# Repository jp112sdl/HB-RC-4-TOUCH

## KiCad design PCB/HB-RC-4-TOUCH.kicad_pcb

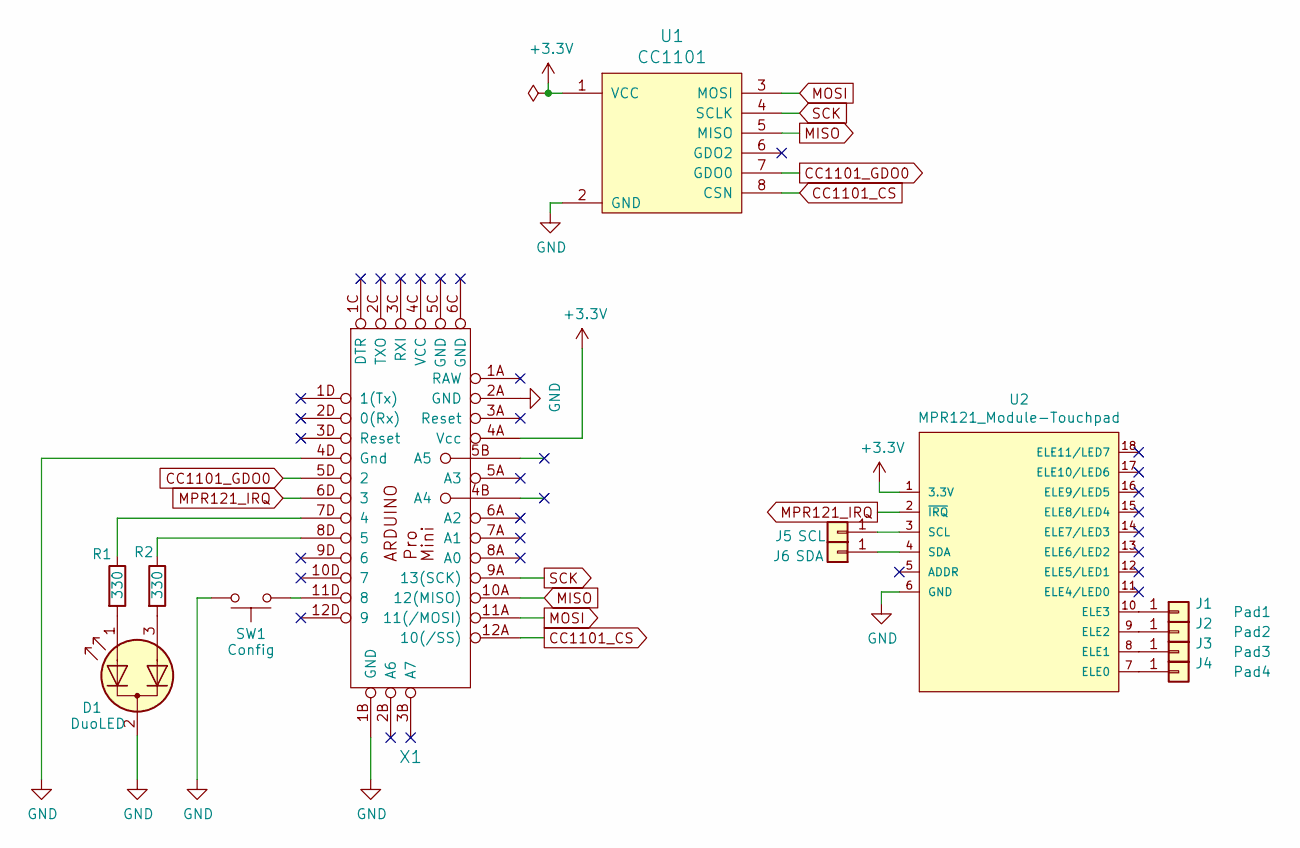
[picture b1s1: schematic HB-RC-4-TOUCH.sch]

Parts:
D1: DuoLED; LED_D3.0mm-3
J1: Pad1; TOUCH_PAD_46x46
J2: Pad2; TOUCH_PAD_46x46
J3: Pad3; TOUCH_PAD_46x46
J4: Pad4; TOUCH_PAD_46x46
J5: SCL; TestPoint_Pad_1.5x1.5mm
J6: SDA; TestPoint_Pad_1.5x1.5mm
R1, R2: 330; R_0805_2012Metric_Pad1.15x1.40mm_HandSolder
SW1: Config; SW_SPST_FSMSM
U1: CC1101; CC1101_Pads
U2: MPR121_Module-Touchpad; MPR121_SMD
X1: Arduino_Pro_Mini

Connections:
+3V3: U1.1 (VCC), U2.1 (3.3V), X1.4A (Vcc)
CC1101_CS: U1.8 (CSN), X1.12A (10(/SS))
CC1101_GDO0: U1.7 (GDO0), X1.5D (2)
GND: D1.2 (K), SW1.2, U1.2 (GND), U2.6 (GND), X1.1B (GND), X1.2A (GND), X1.4D (Gnd)
MISO: U1.5 (MISO), X1.10A (12(MISO))
MOSI: U1.3 (MOSI), X1.11A (11(/MOSI))
MPR121_IRQ: U2.2 (~IRQ), X1.6D (3)
unnamed: D1.1 (A1), R1.2
unnamed: D1.3 (A2), R2.2
unnamed: J1.1, U2.10 (ELE3)
unnamed: J2.1, U2.9 (ELE2)
unnamed: J3.1, U2.8 (ELE1)
unnamed: J4.1, U2.7 (ELE0)
unnamed: J5.1, U2.3 (SCL)
unnamed: J6.1, U2.4 (SDA)
unnamed: R1.1, X1.7D (4)
unnamed: R2.1, X1.8D (5)
unnamed: SW1.1, X1.11D (8)
SCK: U1.4 (SCLK), X1.9A (13(SCK))

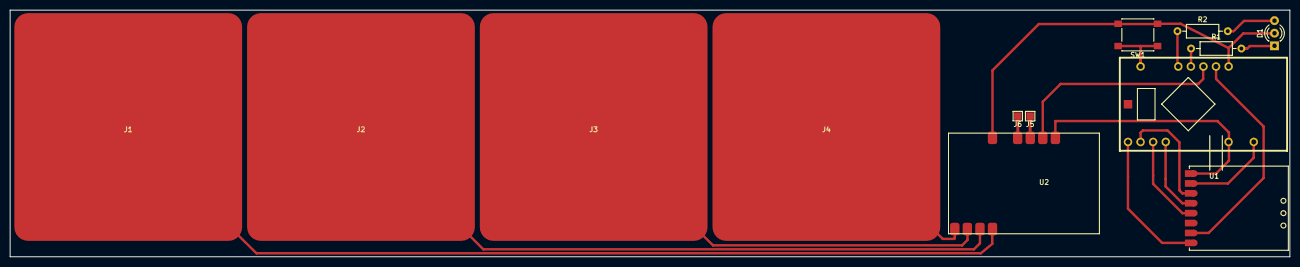
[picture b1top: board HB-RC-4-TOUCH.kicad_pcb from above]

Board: 2 copper layers, 258.4 x 49.8 mm, 13 parts (0 on the bottom side), 19 nets.

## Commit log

2021-01-22 update pcb
2021-01-22 add debug message
2021-01-22 modified pins
2022-01-12 update kicad
